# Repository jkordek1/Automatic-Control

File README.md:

# Analog Control Systems Laboratory PCBs

A collection of educational printed circuit boards (PCBs) developed for laboratory exercises in **Automatic Control Systems**. The project demonstrates the implementation of fundamental analog transfer functions using passive components and operational amplifiers.

The boards are intended for university courses and provide a hands-on platform for studying the behavior of basic dynamic systems through practical experiments.

---

## Overview

This repository contains three independent laboratory boards:

| Board | Description |
|-------|-------------|
| **RC Network** | Passive first-order RC circuit for studying time constants, transient response, and frequency response. |
| **P / PT1 / DT1** | Active analog circuit implementing proportional (P), first-order lag (PT1), and derivative (DT1) transfer functions using operational amplifiers. |
| **PI / I Controller** | Active analog circuit implementing an integrator (I) and proportional-integral (PI) controller. |

---

## Features

- Educational design for laboratory use
- Through-hole components for easy assembly and maintenance
- Banana connector interface for convenient measurements
- Powered from ±12 V laboratory power supply
- Designed in KiCad
- Fully documented schematics and PCB layouts

---

## Boards

### 1. RC Network

A passive first-order RC circuit used to investigate:

- Step response
- Time constant
- Charging and discharging behavior
- Frequency response
- First-order transfer functions

---

### 2. P / PT1 / DT1 Board

An operational amplifier based circuit providing three selectable transfer functions:

- **P** – Proportional element
- **PT1** – First-order lag element
- **DT1** – Derivative element with first-order filtering

Jumper Configuration:
| Transfer Function | JP1 | JP2 |
|-------------------|-----|-----|
| **PT1** | Pins **2–3** | Pins **2–3** |
| **DT1** | Pins **1–2** | Pins **1–2** |
| **P** | Pins **2–3** | Pins **1–2** |

This board allows students to compare the behavior of different dynamic systems under identical experimental conditions.

---

### 3. PI / I Controller

An operational amplifier implementation of:

- **Integrator (I)**
- **Proportional–Integral (PI) controller**

Jumper Configuration:
| Transfer Function | JP1 |
|-------------------|:---:|
| **PI** | 1–2 |
| **I** | 2–3 |

The board is intended for experiments involving closed-loop control and controller tuning.

## Software

Designed using **KiCad**.

The repository includes:

- Schematics
- PCB layouts
- Gerber files
- Bill of Materials (BOM)
- Manufacturing files

---

## Applications

These boards are suitable for:

- Automatic Control Systems laboratories
- Analog Electronics courses
- Control Engineering education
- Demonstrations of transfer functions
- Experimental verification of theoretical models

---

## Future Improvements

Planned additions include:

- Laboratory manuals
- Example experiments
- Simulation models
- Oscilloscope measurements
- Bode plots
- Assembly instructions

---

## License

This project is released under the MIT License.

---

## Author

Designed and developed for educational use in Automatic Control Systems laboratories.

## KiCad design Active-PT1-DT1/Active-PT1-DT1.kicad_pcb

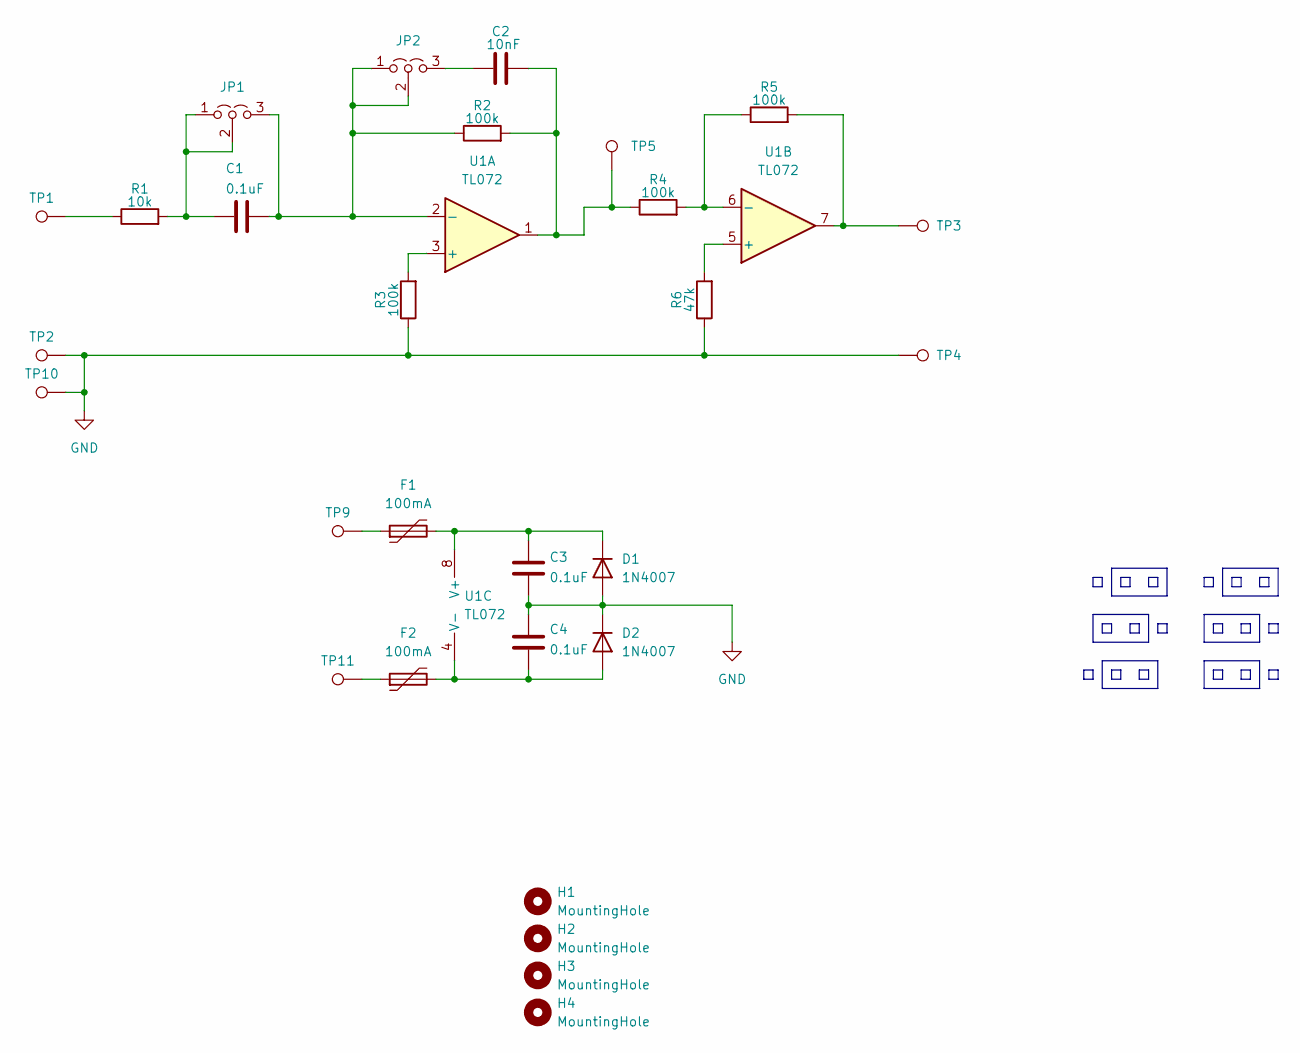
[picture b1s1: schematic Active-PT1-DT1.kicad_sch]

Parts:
C1, C3, C4: 0.1uF; C_Rect_L7.2mm_W2.5mm_P5.00mm
C2: 10nF; C_Rect_L7.2mm_W2.5mm_P5.00mm
D1, D2: 1N4007; D_DO-41_SOD81_P10.16mm_Horizontal
F1, F2: 100mA; C_Disc_D7.5mm_W4.4mm_P5.00mm
H1, H2, H3, H4: MountingHole; MountingHole_3.2mm_M3
JP1, JP2: Jumper_3_Open; Jumper_1x03
R1: 10k; R_Axial_DIN0207_L6.3mm_D2.5mm_P10.16mm_Horizontal
R2, R3, R4, R5: 100k; R_Axial_DIN0207_L6.3mm_D2.5mm_P10.16mm_Horizontal
R6: 47k; R_Axial_DIN0207_L6.3mm_D2.5mm_P10.16mm_Horizontal
TP1, TP3, TP5: TestPoint; DELTRON 4mm banana socket - red
TP2, TP4, TP10: TestPoint; DELTRON 4mm banana socket - black
TP9: TestPoint; DELTRON 4mm banana socket - yellow
TP11: TestPoint; DELTRON 4mm banana socket - blue
U1: TL072; DIP-8_W7.62mm_LongPads

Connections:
GND: C3.2, C4.1, D1.2 (A), D2.1 (K), R3.1, R6.1, TP2.1 (1_1), TP4.1 (1_1), TP10.1 (1_1)
unnamed: C2.2, R2.2, R4.1, TP5.1 (1_1), U1.1
unnamed: C3.1, D1.1 (K), F1.2, U1.8 (V+)
unnamed: C4.2, D2.2 (A), F2.2, U1.4 (V-)
unnamed: F1.1, TP9.1 (1_1)
unnamed: F2.1, TP11.1 (1_1)
unnamed: C1.1, JP1.1 (A), JP1.2 (C), R1.2
unnamed: C1.2, JP1.3 (B), JP2.1 (A), JP2.2 (C), R2.1, U1.2 (-)
unnamed: C2.1, JP2.3 (B)
unnamed: R1.1, TP1.1 (1_1)
unnamed: R5.2, TP3.1 (1_1), U1.7
unnamed: R3.2, U1.3 (+)
unnamed: R6.2, U1.5 (+)
unnamed: R4.2, R5.1, U1.6 (-)

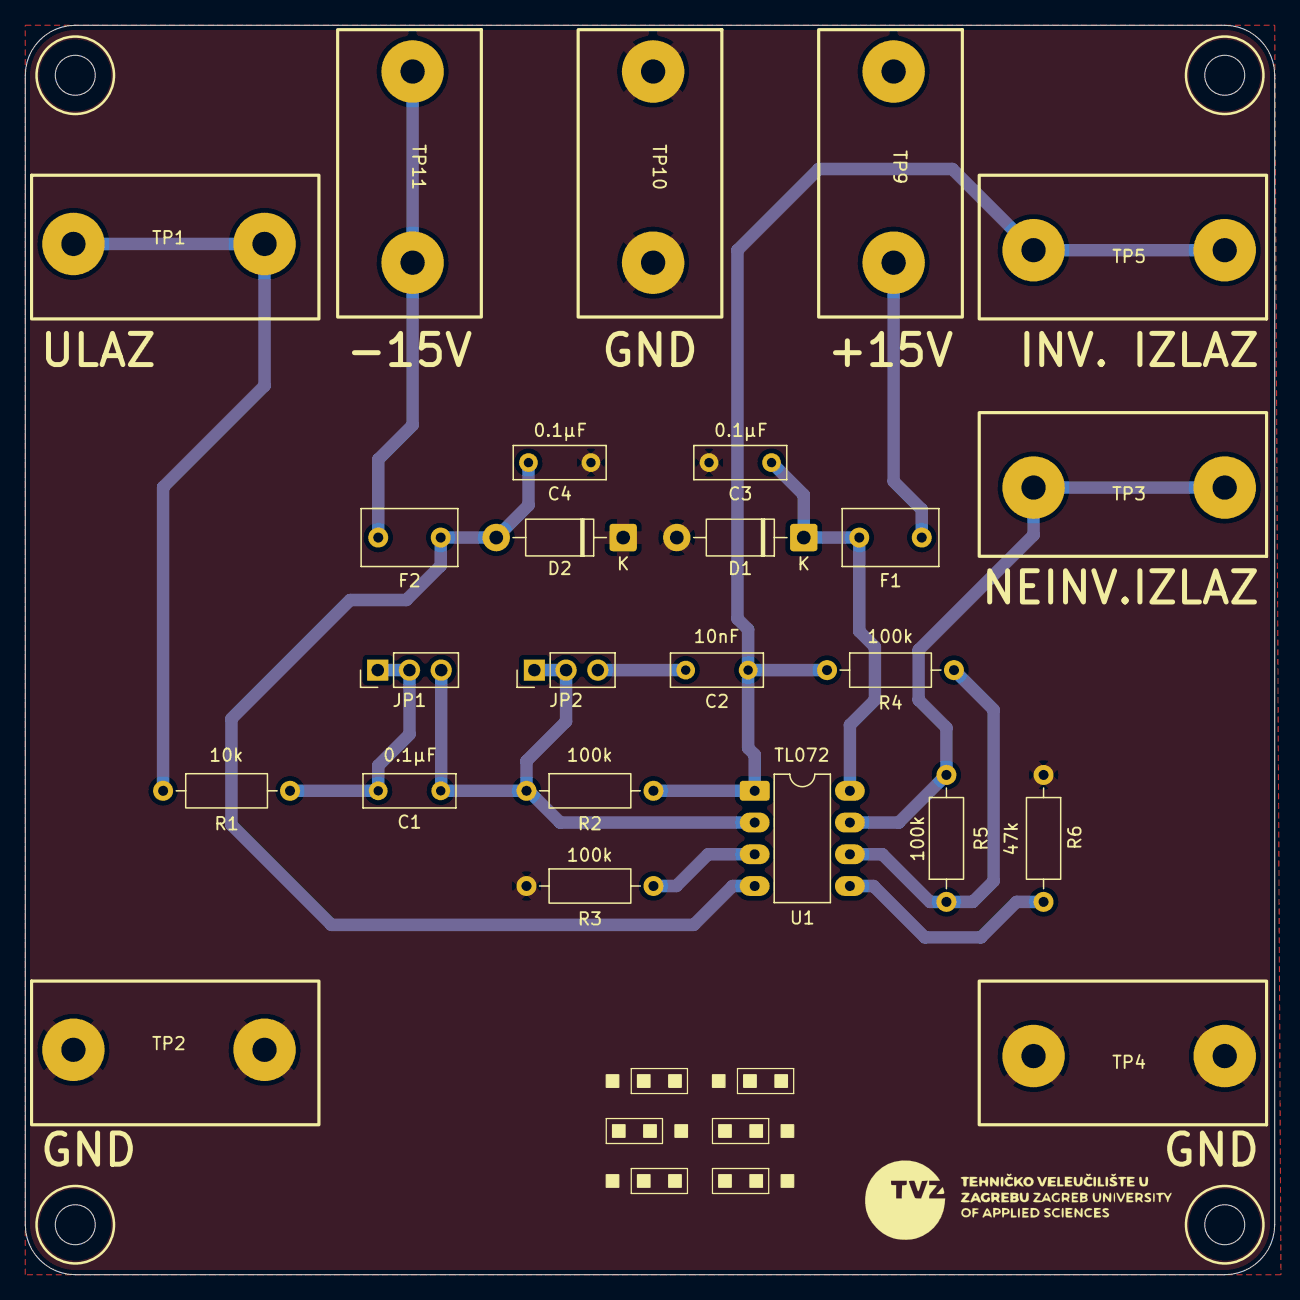
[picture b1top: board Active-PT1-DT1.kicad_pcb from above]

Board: 2 copper layers, 100.0 x 100.0 mm, 29 parts (0 on the bottom side), 14 nets.

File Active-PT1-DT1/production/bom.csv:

Designator,Footprint,Quantity,Value,LCSC Part #
"C1, C3, C4",C_Rect_L7.2mm_W2.5mm_P5.00mm,3,0.1uF,
C2,C_Rect_L7.2mm_W2.5mm_P5.00mm,1,10nF,
"D1, D2",D_DO-41_SOD81_P10.16mm_Horizontal,2,1N4007,
"F1, F2",C_Disc_D7.5mm_W4.4mm_P5.00mm,2,100mA,
R1,R_Axial_DIN0207_L6.3mm_D2.5mm_P10.16mm_Horizontal,1,10k,
"R2, R3, R4, R5",R_Axial_DIN0207_L6.3mm_D2.5mm_P10.16mm_Horizontal,4,100k,
R6,R_Axial_DIN0207_L6.3mm_D2.5mm_P10.16mm_Horizontal,1,47k,
"TP1, TP3, TP5",DELTRON 4mm banana socket - red,3,TestPoint,
"TP10, TP2, TP4",DELTRON 4mm banana socket - black,3,TestPoint,
TP11,DELTRON 4mm banana socket - blue,1,TestPoint,
TP9,DELTRON 4mm banana socket - yellow,1,TestPoint,
U1,DIP-8_W7.62mm_LongPads,1,TL072,

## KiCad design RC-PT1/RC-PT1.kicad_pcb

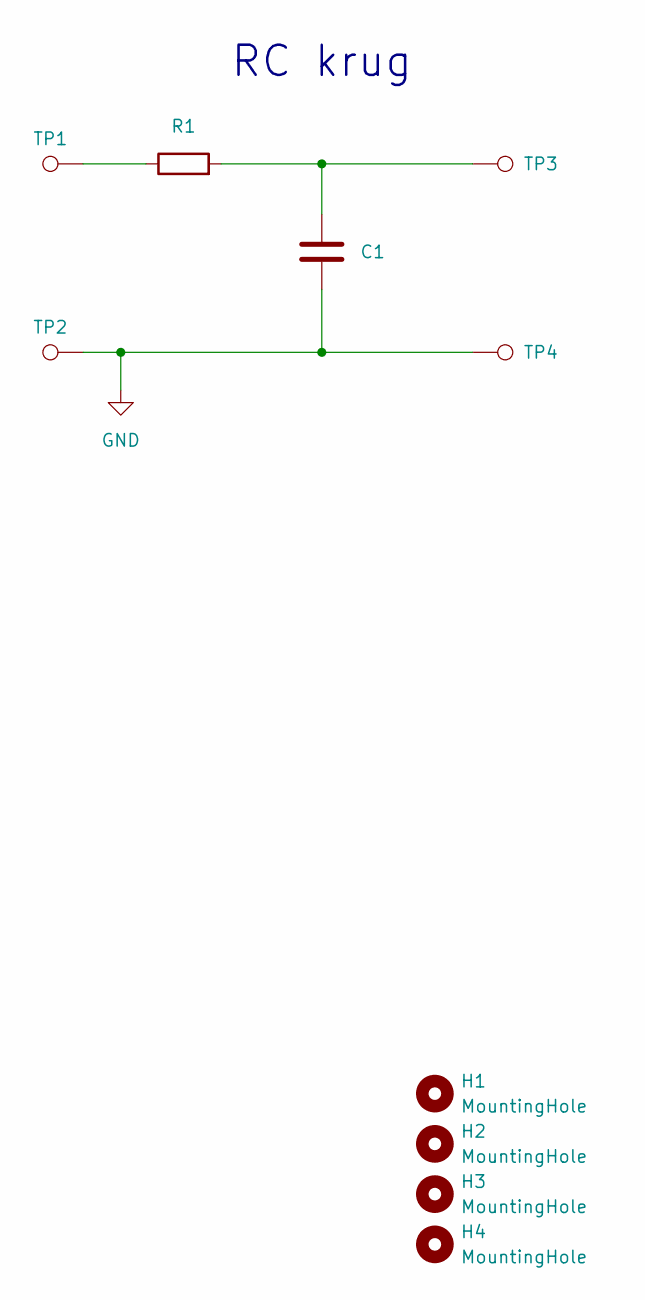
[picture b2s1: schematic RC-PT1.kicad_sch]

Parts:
C1: C; C_Rect_L7.2mm_W5.0mm_P5.00mm
H1, H2, H3, H4: MountingHole; MountingHole_3.2mm_M3
R1: R; R_Axial_DIN0207_L6.3mm_D2.5mm_P10.16mm_Horizontal
TP1, TP3: TestPoint; DELTRON 4mm banana socket - red
TP2, TP4: TestPoint; DELTRON 4mm banana socket - black

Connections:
GND: C1.2, TP2.1 (1_1), TP4.1 (1_1)
unnamed: C1.1, R1.2, TP3.1 (1_1)
unnamed: R1.1, TP1.1 (1_1)

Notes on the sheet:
RC krug

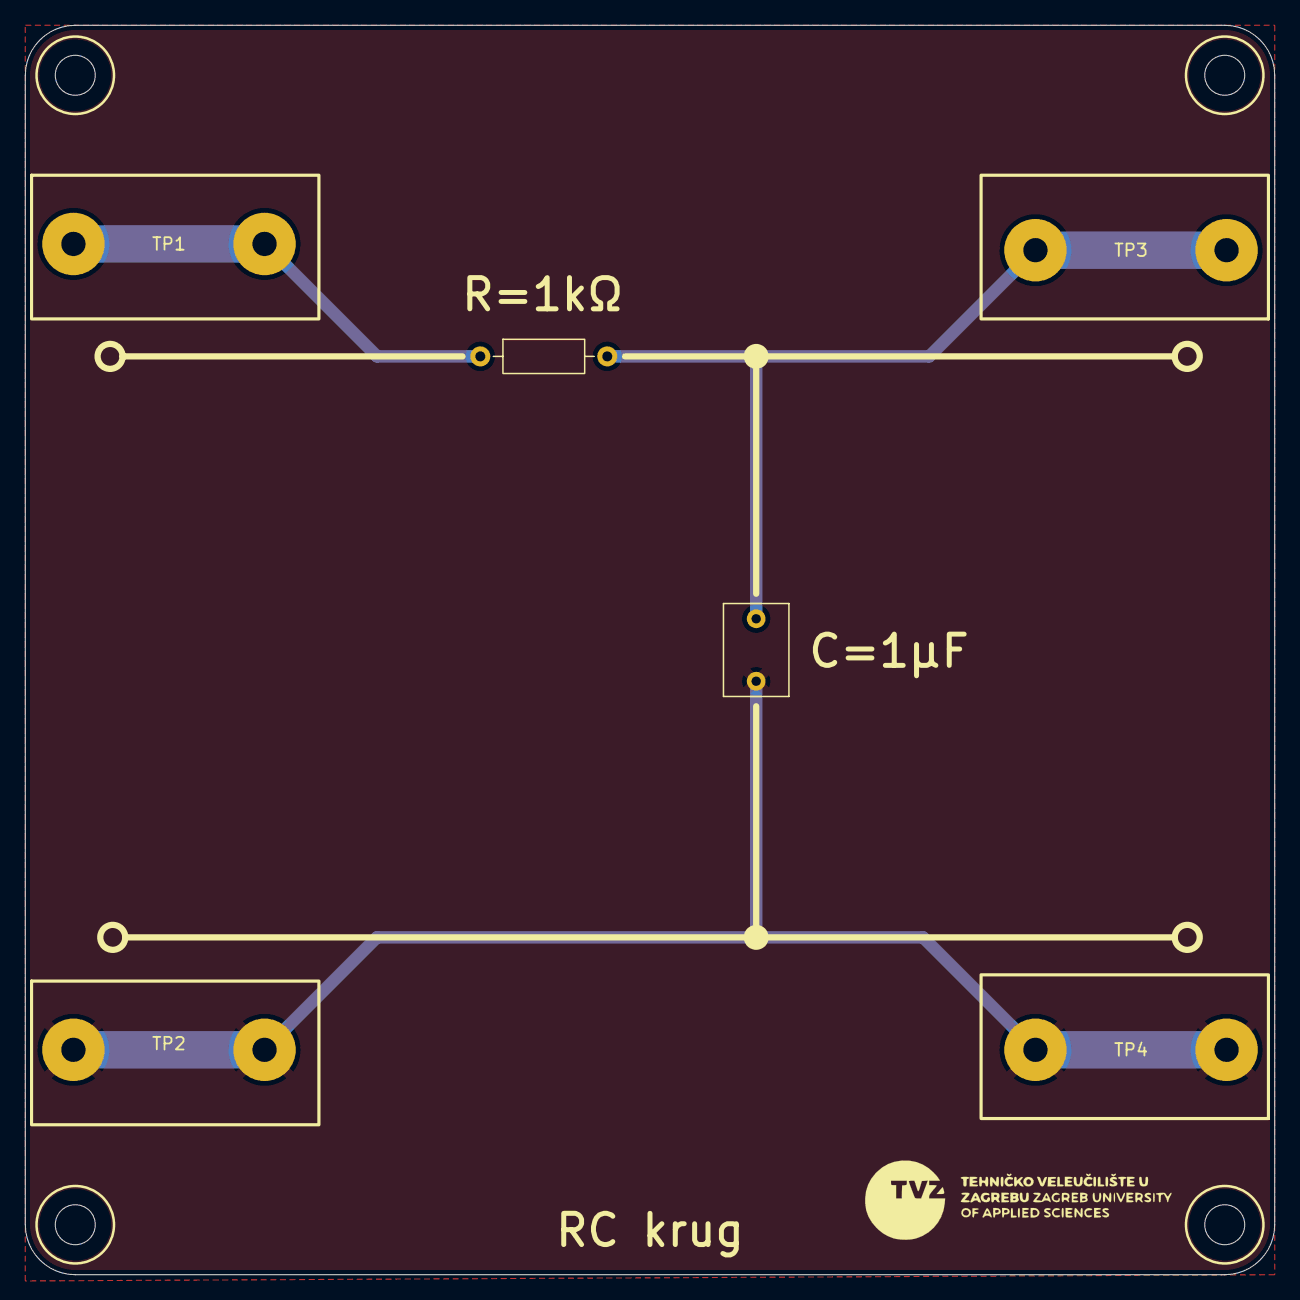
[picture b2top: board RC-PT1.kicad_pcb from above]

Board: 2 copper layers, 100.0 x 100.0 mm, 10 parts (0 on the bottom side), 3 nets.

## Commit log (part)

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2026-06-23 Pastivni PT1
2026-06-24 DT1 added
2026-06-25 remove DT1
2026-06-25 Dodan aktivni član PT1/DT1
2026-06-26 PT1/DT1/P
2026-06-27 Fix libraries
2026-06-29 PT1/DT1/P complete
2026-06-29 Logos
2026-06-30 gerber
2026-06-30 Images
